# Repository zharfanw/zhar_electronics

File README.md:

# zhar_electronics
Database of Zharfan's Electronics 

## Tools 
  1. KiCAD
  2. Altium
  3. EasyEDA

## Electronics Theme
### Power Distribution Module MOSFET DC
  1. [Single Switch PDM](/SingleSwitchControlPDM/)
  2. 
### Power Distribution Module Relay
  1. Single Relay :soon:
  2. 4 Channel Relay :soon:
  3. 8 Channel Relay :soon:
  4. 8 Channel Relay via I2C :soon:
### ESP32 Universe
  1. [ESP32 Raw](/ESP32Raw/)
### At Tiny uC Universe
  1. [At Tiny Raw](/AtTinyRaw_1) 
  2. [At Tiny 3216 DevBoard](/ATTiny3216_DevBoard) 
### Power Button 
  1. [External Latch Power Button](/ExternalLatchPowerButton_Raw)
  2. [Smart Power Button Latch](/LTC2954_ModuleConnector/)
  3. [Latch Power Button with Trigger](/LatchPowerButtonWithTrig_Module/)
### DCDC Converter
  1. [Non Inverting Buck Boost Converter SEPIC MT3608](/Non%20Inverting%20Buck_Boost%20Converter%20Sepic%20MT3608/) 
  2. [78xx Replacement](/78xx%20Replacement/)
  3. [DCDC Boost Converter XL6009](/DCDC%20Boost%20Converter%20XL6009/)

### Power Bank Batttery Management System
 1. [Power Bank IP5306](/PowerBank_IP5306)

### Instrumentation Signal Conditioning
 1. 4-20mA to 0-5v Converter :soon:
 2. 4-20mA to 0-3v Converter :soon:
 5. Inverting Op Amp
 6. Non-Inverting Op Amp

### Display 
  1. OLED
  2. 7 Segment
  3. Dot Matrix
  4. HMI
  5. LCD

### Sensor IC
  1. MPU6050
  2. Accelerometer
  3. Barometric
  4. 

### Analog Multiplexer :soon:
:arrows_counterclockwise:
### Digital Multiplexer :soon:
:arrows_counterclockwise:
### Signal Generator :soon:
:arrows_counterclockwise:
### DC Motor Controller :soon:
:arrows_counterclockwise:
### Formula Student :soon:
:arrows_counterclockwise:

### Engine Ignition System :soon:
:arrows_counterclockwise:
### Mosfet Driver :soon:
:arrows_counterclockwise:

## Regerence Design

### Multimeter/Oscilloscope 
  1. [STM32 Scopev1](https://oshwlab.com/radiohonza/stm32ez-scopev1_copy)
  2. [STM32 Multimeter](https://hackaday.io/project/165857-stm32-open-source-multimeter)

### Nucleo Series STM32 (Need to Copy)()
 1. [Nucleo 64 STM32F446RE]
 2. [Nucleo 144 STM32]

### BLDC/PMSM/AC Motor Controller :soon:
  1. [Referensi VESC Controller](https://github.com/paltatech/VESC-controller)
  2. 

### Engine Control Unit
 1. [Referensi Speeduino](https://github.com/speeduino)
 2. [Referensi rusEFI](https://github.com/rusefi)

### FPGA Board by Olimex
 1. [Referensi Olimex](https://github.com/OLIMEX/iCE40HX8K-EVB)
 2. [Referensi Olimex 1](https://github.com/OLIMEX/iCE40HX1K-EVB)
 3. [Referensi Olimex FPGA Daughter ADC](https://www.olimex.com/Products/FPGA/iCE40/iCE40-ADC/open-source-hardware)
 4. [Referensi Olimex FPGA Daughter DAC](https://www.olimex.com/Products/FPGA/iCE40/iCE40-DAC/open-source-hardware)
 5. [Referensi Olimex FPGA Daughter VGA, PS/2 and IrDA link](https://www.olimex.com/Products/FPGA/iCE40/iCE40-IO/open-source-hardware)
 6. [Referensi Olimex FPGA Daughter DIO](https://www.olimex.com/Products/FPGA/iCE40/iCE40-DIO/open-source-hardware)

### Referensi from Wagiminator(Need To Copy) (2/66 Coppied)
 1. [IP5306 LiPo Charger Booster SMD (Copied)](https://oshwlab.com/wagiminator/y-ip5306-lipo-charger-booster)
 2. [ATmega SolderingStation SMD v2](https://oshwlab.com/wagiminator/z-solderingstation-smd-v2)
 3. [ATmega TransistorTester SMD](https://oshwlab.com/wagiminator/y-atmega-transistortester-smd)
 4. [ATtiny84 TinyHVSP SMD](https://oshwlab.com/wagiminator/z-attiny84-tinyhvprogrammer)
 5. [y-atmega-eeprom-programmer](https://oshwlab.com/wagiminator/y-atmega-eeprom-programmer)
 6. [y-attiny814-power-analyzer](https://oshwlab.com/wagiminator/y-attiny814-power-analyzer
)
 7. (https://oshwlab.com/wagiminator/adum3160-usb-isolator
)
8. (https://oshwlab.com/wagiminator/attiny13-tinytacho
)

9. (https://oshwlab.com/wagiminator/attiny13-tinyups-smd
)

10. (https://oshwlab.com/wagiminator/attiny85-phone-charge-guard
)
11. (https://oshwlab.com/wagiminator/samd21e-development-board
)

12. (https://oshwlab.com/wagiminator/attiny814-nrf2usb
)

13. (https://oshwlab.com/wagiminator/y-attiny10-development-board-smd
)

14. [IP5306 LiPo Charger Booster USB-C (Copied)](https://oshwlab.com/wagiminator/ip5306-lipo-charger-booster-usb-c
)

15. (https://oshwlab.com/wagiminator/lipo-charger-protector-booster_copy
)

17. (https://oshwlab.com/wagiminator/attiny13-tinyremoteir-xl
)

18. (https://oshwlab.com/wagiminator/y-mt3608-12v-boost-converter
)
19. (https://oshwlab.com/wagiminator/attiny1604-updi-hv-programmer
)
20. (https://oshwlab.com/wagiminator/tp4056-lipo-charger-ls
)
21. (https://oshwlab.com/wagiminator/y-lm2596-5vbuckconverter-smd
)
22. (https://oshwlab.com/wagiminator/y-tp4056-lir2032-charger
)
23. (https://oshwlab.com/wagiminator/y-mp2307-5vbuckconverter-smd
)
24. (https://oshwlab.com/wagiminator/y-attiny13-soldering-station-smd
)
25. (https://oshwlab.com/wagiminator/z-mc34063-5v-buckconverter
)
26. (https://oshwlab.com/wagiminator/cn3058-lifepo4-power-board-ls-3v3
)
27. (https://oshwlab.com/wagiminator/cn3058-lifepo4-power-board-ls-5v
)
28. (https://oshwlab.com/wagiminator/tp4056-lipo-charger-protector-power-booster_copy_copy
)
29. (https://oshwlab.com/wagiminator/attiny84-tinycalibrator
)
30. (https://oshwlab.com/wagiminator/attiny13-tinyradio
)
31. (https://oshwlab.com/wagiminator/attiny85-usb-c-tester
)
32. (https://oshwlab.com/wagiminator/tp4056-lipo-charger-protector-power-booster_copy
)
33. (https://oshwlab.com/wagiminator/y-cn3801-lifepo4-solar-charger_copy_copy
)
34. (https://oshwlab.com/wagiminator/attiny814-usb-rtc
)
35. (https://oshwlab.com/wagiminator/y-attiny85-electronic-load
)
36. (https://oshwlab.com/wagiminator/z-lifepo4-charger
)
37. (https://oshwlab.com/wagiminator/lipo-charger-protector-booster
)
38. (https://oshwlab.com/wagiminator/fp6277-power-bank
)
39. (https://oshwlab.com/wagiminator/pyupdi-programmer_copy_copy
)
40. (https://oshwlab.com/wagiminator/pyupdi-programmer
)
41. (https://oshwlab.com/wagiminator/atmega-updi-hv-programmer
)
42. (https://oshwlab.com/wagiminator/attiny13-tinyremote-rf
)

43. (https://oshwlab.com/wagiminator/attiny-814-development-board-smd
)

44. (https://oshwlab.com/wagiminator/y-tps61169-boost-led-driver
)

45. (https://oshwlab.com/wagiminator/attiny84-development-board-smd
)

46. (https://oshwlab.com/wagiminator/y-ch330-usb2serialconverter-3v3-smd
)

47. (https://oshwlab.com/wagiminator/samd11c-swd-programmer
)

48. (https://oshwlab.com/wagiminator/mp2307-usb-c-buck-converter
)

49. (https://oshwlab.com/wagiminator/attiny45-usbtinyisp-smd
)

50. (https://oshwlab.com/wagiminator/attiny1604-updi-programmer
)

51. (https://oshwlab.com/wagiminator/y-cn3058-lifepo4-charger-booster
)

52. (https://oshwlab.com/wagiminator/samd11d-development-board
)

53. (https://oshwlab.com/wagiminator/y-attiny45-usbtinyisp
)

54. (https://oshwlab.com/wagiminator/y-max3000-altera-cpld-development-board_copy
)

55. (https://oshwlab.com/wagiminator/samd11c-development-board
)

56. (https://oshwlab.com/wagiminator/swd-programmer-adapter
)

57. (https://oshwlab.com/wagiminator/attiny85-development-board-dip
)
58. (https://oshwlab.com/wagiminator/attiny85-development-board-smd
)
59. (https://oshwlab.com/wagiminator/attiny-814-development-board-smd_copy
)
60. (https://oshwlab.com/wagiminator/attiny412-5v-isolated-dc-dc-converter
)
61. (https://oshwlab.com/wagiminator/attiny412-5v-isolated-dual-supply
)
62. (https://oshwlab.com/wagiminator/1541-ii-power-guard
)
63. (https://oshwlab.com/wagiminator/ip2312-li-ion-charger
)
64. (https://oshwlab.com/wagiminator/usb-power-filter
)
65. (https://oshwlab.com/wagiminator/attiny412-usb-pd-inverter
)
66. (https://oshwlab.com/wagiminator/ip6520-usb-pd-source)

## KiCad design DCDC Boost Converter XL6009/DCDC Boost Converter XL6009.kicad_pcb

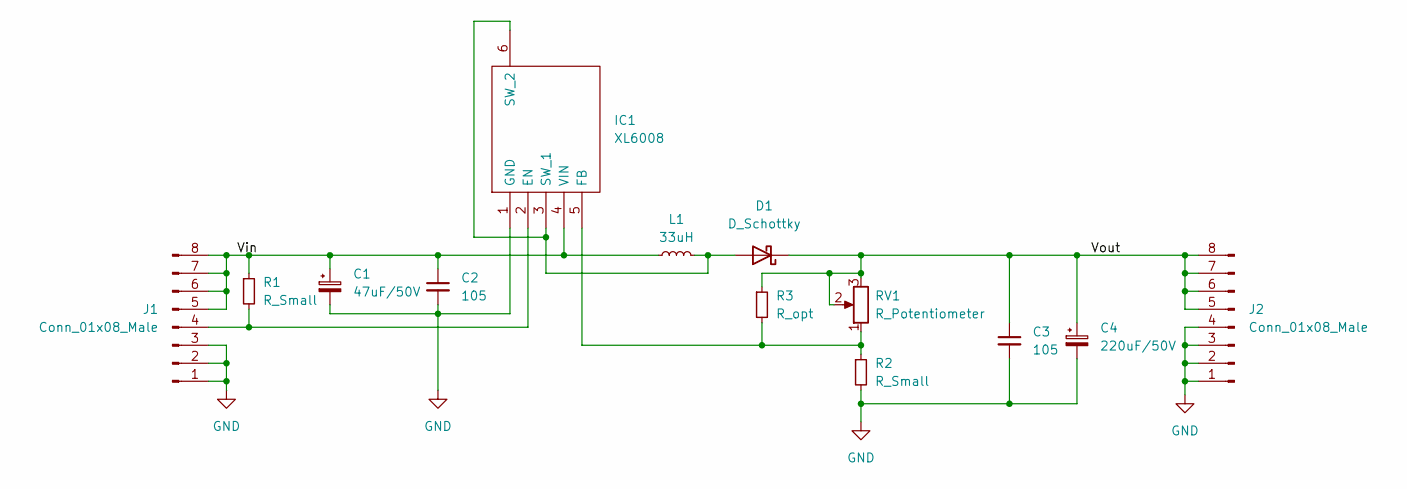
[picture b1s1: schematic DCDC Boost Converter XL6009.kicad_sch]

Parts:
C1: 47uF/50V; CP_Elec_6.3x5.9
C2, C3: 105; C_0805_2012Metric_Pad1.18x1.45mm_HandSolder
C4: 220uF/50V; CP_Elec_6.3x5.9
D1: D_Schottky; D_SMA-SMB_Universal_Handsoldering
IC1: XL6008; Manufacturer_Part_Number XL6008
J1, J2: Conn_01x08_Male; PinSocket_1x08_P2.54mm_Vertical
L1: 33uH; L_10.4x10.4_H4.8
R1, R2: R_Small; R_0805_2012Metric_Pad1.20x1.40mm_HandSolder
R3: R_opt; R_0805_2012Metric_Pad1.20x1.40mm_HandSolder
RV1: R_Potentiometer; Potentiometer_Bourns_3296W_Vertical

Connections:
/Vin: C1.1, C2.1, IC1.4 (VIN), J1.5, J1.6, J1.7, J1.8, L1.1, R1.1
/Vout: C3.1, C4.1, D1.1 (K), J2.5, J2.6, J2.7, J2.8, R3.1, RV1.2, RV1.3
GND: C1.2, C2.2, C3.2, C4.2, IC1.1 (GND), J1.1, J1.2, J1.3, J2.1, J2.2, J2.3, J2.4, R2.2
unnamed: D1.2 (A), IC1.3 (SW_1), IC1.6 (SW_2), L1.2
unnamed: IC1.2 (EN), J1.4, R1.2
unnamed: IC1.5 (FB), R2.1, R3.2, RV1.1

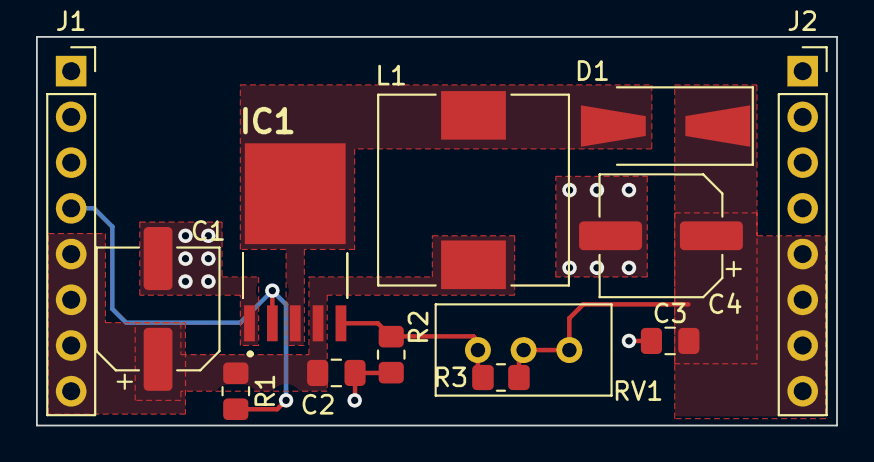
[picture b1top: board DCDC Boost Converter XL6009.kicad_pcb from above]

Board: 2 copper layers, 44.5 x 21.6 mm, 13 parts (0 on the bottom side), 6 nets.

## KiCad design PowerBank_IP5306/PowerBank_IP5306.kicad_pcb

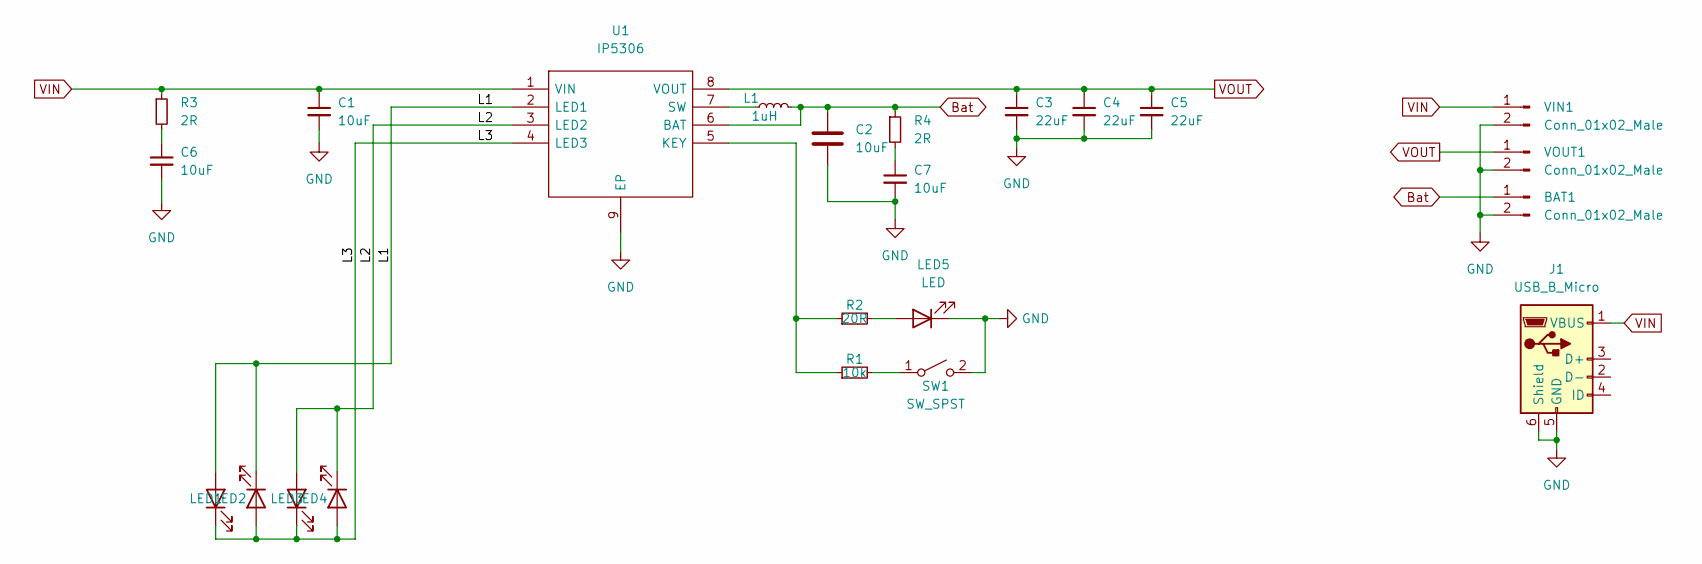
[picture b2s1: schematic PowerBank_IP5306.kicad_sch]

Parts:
BAT1: Conn_01x02_Male; PinHeader_1x02_P2.54mm_Vertical
C1, C2, C6, C7: 10uF; C_0805_2012Metric
C3, C4, C5: 22uF; C_0805_2012Metric
J1: USB_B_Micro; USB_Micro-B_Molex-105017-0001
L1: 1uH
LED1, LED2, LED3, LED4, LED5: LED; D_0805_2012Metric
R1: 10k; R_0805_2012Metric
R2: 20R; R_0805_2012Metric
R3, R4: 2R; R_0805_2012Metric
SW1: SW_SPST; SW_SPST_B3U-1000P
U1: IP5306; SOIC127P600X165-9N; Manufacturer_Part_Number IP5306
VIN1: Conn_01x02_Male; PinHeader_1x02_P2.54mm_Vertical
VOUT1: Conn_01x02_Male; PinHeader_1x02_P2.54mm_Vertical

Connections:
/L1: LED1.2 (A), LED2.1 (K), U1.2 (LED1)
/L2: LED3.2 (A), LED4.1 (K), U1.3 (LED2)
/L3: LED1.1 (K), LED2.2 (A), LED3.1 (K), LED4.2 (A), U1.4 (LED3)
Bat: BAT1.1, C2.1, L1.2, R4.1, U1.6 (BAT)
GND: BAT1.2, C1.2, C2.2, C3.2, C4.2, C5.2, C6.2, C7.2, J1.5 (GND), J1.6 (Shield), LED5.1 (K), SW1.2 (B), U1.9 (EP), VIN1.2, VOUT1.2
unnamed: L1.1, U1.7 (SW)
unnamed: LED5.2 (A), R2.2
unnamed: R1.2, SW1.1 (A)
unnamed: R1.1, R2.1, U1.5 (KEY)
unnamed: C6.1, R3.2
unnamed: C7.1, R4.2
VIN: C1.1, J1.1 (VBUS), R3.1, U1.1 (VIN), VIN1.1
VOUT: C3.1, C4.1, C5.1, U1.8 (VOUT), VOUT1.1

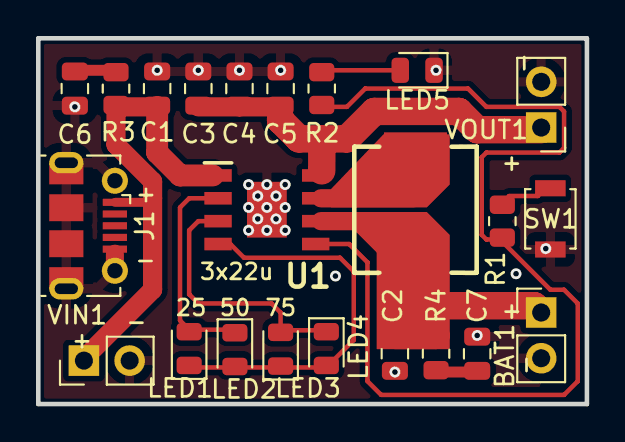
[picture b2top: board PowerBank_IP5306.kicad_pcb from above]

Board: 2 copper layers, 30.5 x 20.3 mm, 23 parts (0 on the bottom side), 13 nets.

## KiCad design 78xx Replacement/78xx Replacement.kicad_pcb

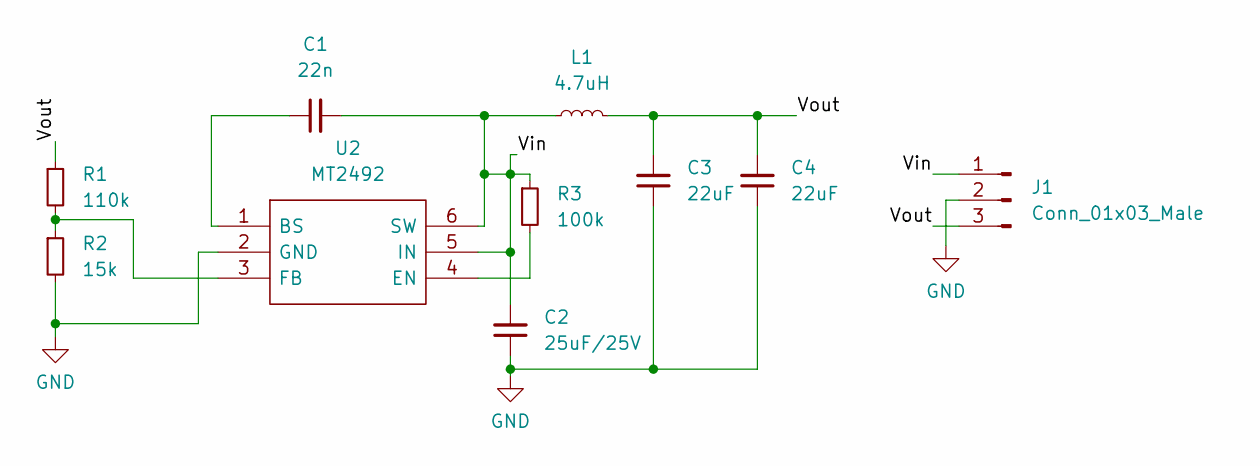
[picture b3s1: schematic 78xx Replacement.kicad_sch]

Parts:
C1: 22n; C_0603_1608Metric
C2: 25uF/25V; C_0603_1608Metric
C3, C4: 22uF; C_0603_1608Metric
J1: Conn_01x03_Male; PinHeader_1x03_P2.54mm_Horizontal
L1: 4.7uH; L_7.3x7.3_H4.5
R1: 110k; R_0805_2012Metric
R2: 15k; R_0805_2012Metric
R3: 100k; R_0805_2012Metric
U2: MT2492; SOT95P280X145-6N; Manufacturer_Part_Number MT2492

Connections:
/Vin: C1.2, C2.2, J1.1, L1.1, R3.1, U2.5 (IN), U2.6 (SW)
/Vout: C3.2, C4.2, J1.3, L1.2, R1.1
GND: C2.1, C3.1, C4.1, J1.2, R2.2, U2.2 (GND)
unnamed: C1.1, U2.1 (BS)
unnamed: R1.2, R2.1, U2.3 (FB)
unnamed: R3.2, U2.4 (EN)

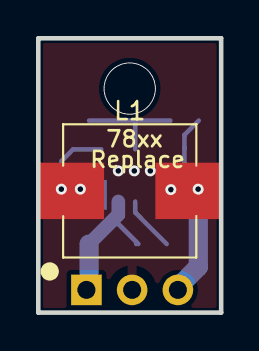
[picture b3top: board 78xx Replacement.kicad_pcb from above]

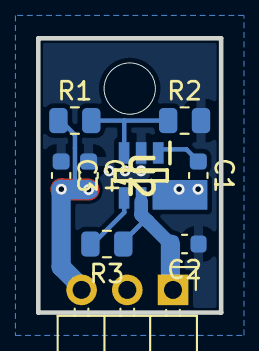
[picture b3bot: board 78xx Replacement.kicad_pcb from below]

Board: 2 copper layers, 10.2 x 15.2 mm, 10 parts (9 on the bottom side), 6 nets.

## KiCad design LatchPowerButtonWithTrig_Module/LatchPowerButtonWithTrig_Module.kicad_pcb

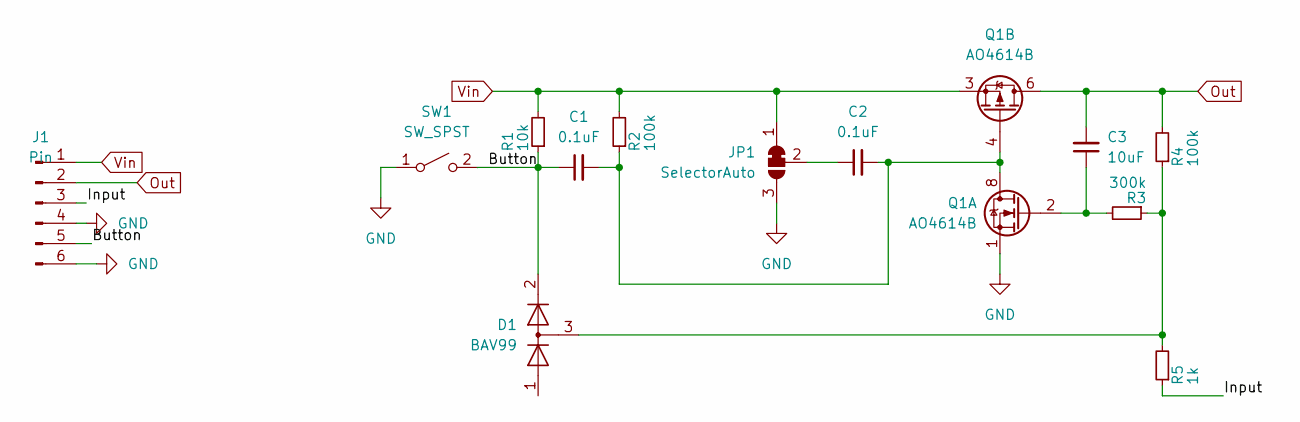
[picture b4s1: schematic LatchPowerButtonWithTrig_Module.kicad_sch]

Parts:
C1, C2: 0.1uF; C_0805_2012Metric_Pad1.18x1.45mm_HandSolder
C3: 10uF; C_1206_3216Metric_Pad1.33x1.80mm_HandSolder
D1: BAV99; SOT-23
J1: Pin; PinHeader_1x06_P2.54mm_Vertical
JP1: SelectorAuto; SolderJumper-3_P1.3mm_Bridged12_Pad1.0x1.5mm
Q1: AO4614B; SOIC-8_3.9x4.9mm_P1.27mm
R1: 10k; R_0805_2012Metric_Pad1.20x1.40mm_HandSolder
R2, R4: 100k; R_0805_2012Metric_Pad1.20x1.40mm_HandSolder
R3: 300k; R_0805_2012Metric_Pad1.20x1.40mm_HandSolder
R5: 1k; R_0805_2012Metric_Pad1.20x1.40mm_HandSolder
SW1: SW_SPST; SW_SPST_CK_RS282G05A3

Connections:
/Button: C1.1, D1.2 (A), J1.5, R1.1, SW1.2 (B)
/Input: J1.3, R5.1
GND: J1.4, J1.6, JP1.3 (B), Q1.1 (S), SW1.1 (A)
unnamed: C1.2, C2.2, Q1.4 (G), Q1.7 (D), Q1.8 (D), R2.1
unnamed: C2.1, JP1.2 (C)
unnamed: C3.1, Q1.2 (G), R3.2
unnamed: D1.3 (K), R3.1, R4.1, R5.2
Out: C3.2, J1.2, Q1.5 (D), Q1.6 (D), R4.2
Vin: J1.1, JP1.1 (A), Q1.3 (1), R1.2, R2.2

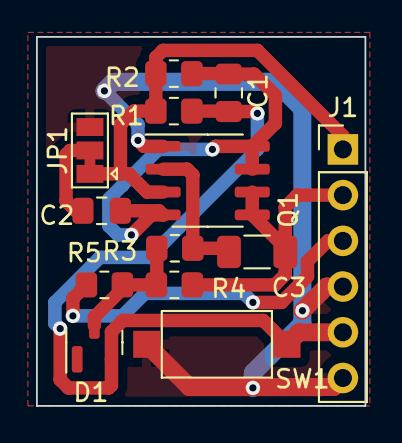
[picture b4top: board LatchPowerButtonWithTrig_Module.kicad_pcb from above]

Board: 2 copper layers, 18.2 x 20.5 mm, 13 parts (0 on the bottom side), 9 nets.

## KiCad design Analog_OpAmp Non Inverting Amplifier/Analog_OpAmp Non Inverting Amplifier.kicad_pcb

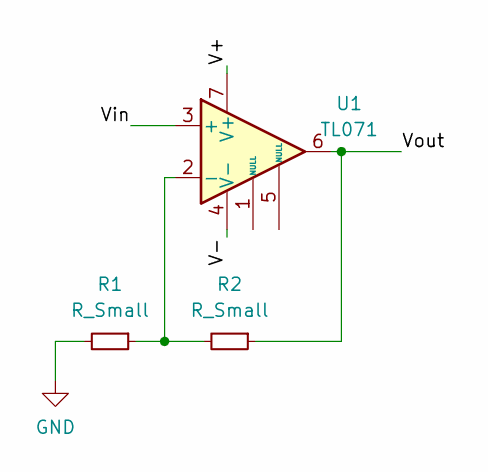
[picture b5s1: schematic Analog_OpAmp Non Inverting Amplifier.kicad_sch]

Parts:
R1, R2: R_Small; R_0805_2012Metric_Pad1.20x1.40mm_HandSolder
U1: TL071; DIP-8_W7.62mm_LongPads

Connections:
/V+: U1.7 (V+)
/V-: U1.4 (V-)
/Vin: U1.3 (+)
/Vout: R2.1, U1.6
GND: R1.2
unnamed: R1.1, R2.2, U1.2 (-)

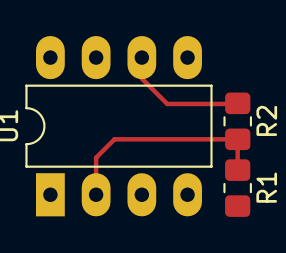
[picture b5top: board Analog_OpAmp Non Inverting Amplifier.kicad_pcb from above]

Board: 2 copper layers, 3 parts (0 on the bottom side), 2 nets.

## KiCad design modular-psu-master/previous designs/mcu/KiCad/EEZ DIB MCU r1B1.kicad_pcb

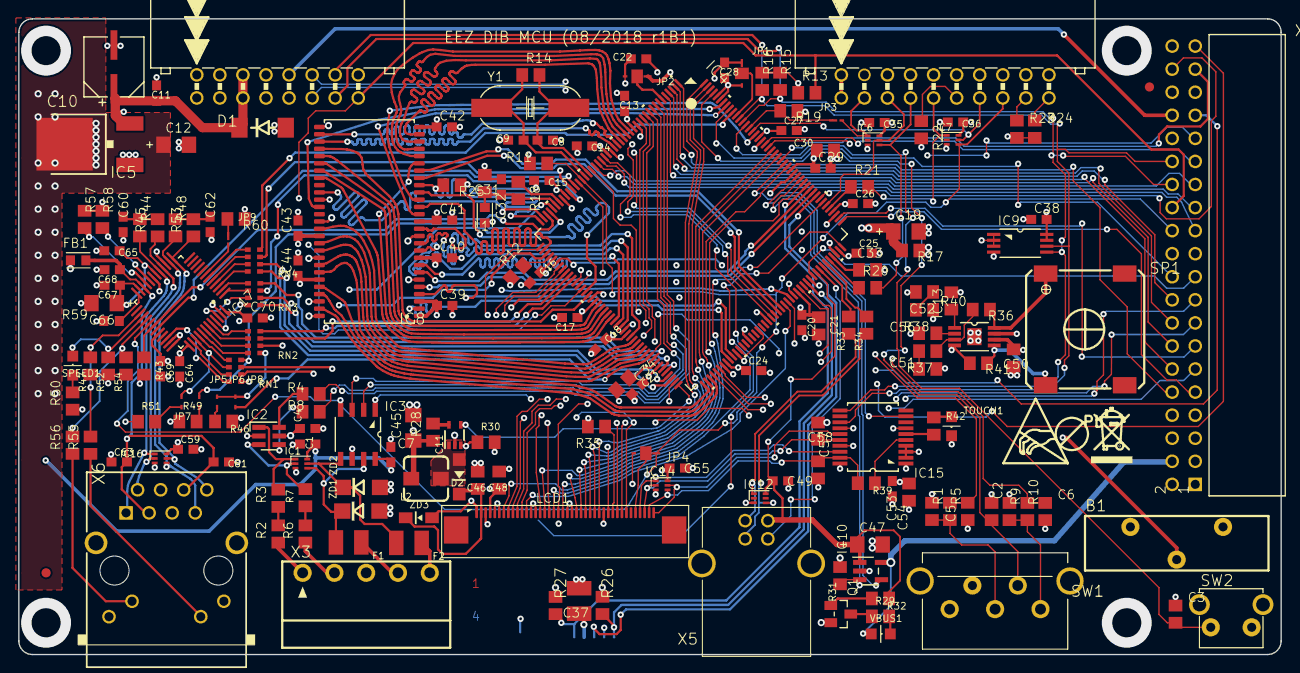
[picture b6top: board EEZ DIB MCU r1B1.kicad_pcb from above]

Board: 4 copper layers, 139.0 x 70.0 mm, 193 parts (0 on the bottom side), 233 nets.

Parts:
B1: DS1092-16-B6P
C1, C4, C7, C11, C13, C14, C15, C16, C17, C18, C20, C23, C24, C25, C26, C27, C28, C29, C32, C35, C36, C38, C39, C40, C41, C42, C43, C44, C49, C53, C55, C59, C60, C61, C62, C63, C64, C65, C67, C68, C69, C70: 100n; C0603
C2, C3, C5, C6, C57, C58: 10n; C0805
C8, C9: 18p; C0603
C10: 47u; CAPAE660X610N
C12, C66: 10u; EC1206
C19: 4u7; EC1206
C21, C30, C31, C46, C50, C54: 1u; C0805
C22: N.C.; C0603
C33, C34, C48: 2u2; C0805
C37: 10u; C1210
C45: 4u7; C1206
C47: 4u7/16V (293D475X9016A2TE3); EC1206
C51, C52: 470n; C0805
C56: 220n; C0805
D1: SMBJ5.0A-TR; DO214AA
D2: NSR0240; SOD123
EEZ_SIGNATURE: SIGNATURESMALL; SIGNATURE_5MM
F1, F2: 50mA; F1210
FB1: 60R@100MHz; BEAD0603
FM1, FM2: FIDUCIAL
IC1, IC6, IC7, IC12, IC14, IC16: TPD4E001DRLR; DRL6
IC2: SN74LVC2G34DBVR; DBV6
IC3: BTS3408G; SOIC127P600X173-8N
IC4: STM32F769IGT6; LQFP-176_24X24MM
IC5: LD1117ADT33TR; DPACK
IC8: IS42S16400J; TSOPII-54
IC9: BR24G64FVT-3AGE2; PW8_TSSOP8
IC10: TPS2051BDBVR; DBV5
IC11: TPS61169DCKR; DCK5
IC13: TPA6205A1DGN; SOP65P490X110-9N
IC15: AR1021-I/SS; SOP65P780X200-20N
IC17: DP83848CVV_NOPB; PT48
J1: 5033981892
JP1, JP2, JP4: JP3-CUT
JP3, JP9: JP2-NOCUT
JP5, JP6, JP7, JP8: JP2-CUT
L1: LCBA-600; BEAD0603
L2: DLG-0403-4R7; DE0403
LCD1: PCA-6-LA-40-HL-3; FPC_40
Q1: MMBT5551; SOT23-BEC
R1, R2, R3, R6, R7, R9, R13, R15, R16, R42: 4K7; R0805
R4, R8: 1K; R0805
R5, R10, R11, R12, R22, R23, R24, R25, R35, R37, R38: 10K; R0805
R14: 1M; R0805
R17: 0R; R0805
R18: 47R; R0805
R19, R26, R27, R29, R31, R32, R40: 47K; R0805
R20, R21, R33, R34: 22R; R0805
R28, R30: 10R; R0805
R36, R39, R41: 20K; R0805
R43: 1K5; R0805
R44, R45, R48, R53: 49R9; R0805
R46, R47, R49, R51, R52, R54, R57, R58, R60: 2K2; R0805
R50, R55, R56: 220R; R0805
R59: 4K87; R0603
RN1, RN2, RN3, RN4: DR1206-33R-4/8; CAY16
SP1: LD-BZEL-M1313
SPEED1: HSMY-C170; LED_0805
SW1: PEC16-2215F-S0024; PEC16-2215F
SW2: BSF-3152; BSF-315X
TOUCH1: HSMY-C170; LED_0805
U$1: RECYCLE_BIN1_8
U$5: PB_SMALL
U$6: ESD_SYMBOL
VBUS1: HSMG-C170; LED_0805
X1: ZL263-40DG
X2: ZL231-16KG; ML16L
X3: 1844249; MC1,5_5-G-3,5
X4: ZL231-20KG; ML20L
X5: 292304-1; USB-B
X6: LMJTAB881243M-L; RJ45-TRAFO-LED
Y1: 10MHz; HC-49_4H
ZD1, ZD2: SMAJ18A; DO214AC
ZD3: BZX384-B30.115; SOD323-W

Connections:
+3V3: C4.1, C12.+, C35.1, C36.1, C37.1, C38.2, C39.1, C40.1, C41.1, C42.1, C43.1, C44.1, C45.1, C48.1, C50.2, C53.2, C54.2, C55.2, C59.1, C69.1, C70.1, FB1.P$1, IC2.5, IC5.4, IC6.6, IC7.6, IC8.1, IC8.3, IC8.9, IC8.14, IC8.27, IC8.43, IC8.49, IC9.1, IC9.2, IC9.3, IC9.7, IC9.8, IC13.6, IC14.6, IC15.1, IC16.6, IC17.32, IC17.48, J1.4, L2.1, LCD1.4, R1.1, R9.1, R13.1, R15.1, R16.1, R17.1, R19.1, R25.1, R26.1, R27.1, R28.1, R31.2, R35.2, R40.2, R43.2, R47.1, R50.1, R51.1, R52.1, R54.1, R57.1, R58.1, R60.1, X1.32, X2.16, X4.1, X4.2, X6.9, X6.12
+3V3(A): C61.2, C63.2, C68.1, FB1.P$2, IC17.22, X6.3, X6.6
+5V: C1.1, C7.2, C10.1, C11.1, D1.C, IC1.6, IC3.8, IC5.3, IC10.5, VBUS1.A, X1.3, X1.4, X2.5, X2.6
+12V: X1.5, X1.6, X2.3, X2.4
/Ethernet PHY/ETH_COL: IC4.47, RN2.2
/Ethernet PHY/ETH_CRS: IC4.40, JP5.1, RN1.4
/Ethernet PHY/ETH_MDC: IC4.33, IC17.31
/Ethernet PHY/ETH_MDIO: IC4.42, IC17.30, R43.1
/Ethernet PHY/ETH_RXD0: IC4.54, RN2.3
/Ethernet PHY/ETH_RXD1: IC4.55, RN2.4
/Ethernet PHY/ETH_RXD2: IC4.83, RN3.1
/Ethernet PHY/ETH_RXD3: IC4.84, RN3.2
/Ethernet PHY/ETH_RX_CLK: IC4.41, RN1.2
/Ethernet PHY/ETH_RX_DV: IC4.53, RN1.3
/Ethernet PHY/ETH_TXD0: IC4.85, RN4.1
/Ethernet PHY/ETH_TXD1: IC4.86, RN4.2
/Ethernet PHY/ETH_TXD2: IC4.34, RN4.3
/Ethernet PHY/ETH_TXD3: IC4.167, RN4.4
/Ethernet PHY/ETH_TX_CLK: IC4.35, RN3.3
/Ethernet PHY/ETH_TX_EN: IC4.80, RN3.4
/Ethernet PHY/LED_ACT: IC17.26, R47.2, R55.2
/Ethernet PHY/LED_LINK: IC17.28, R54.2, R56.2
/Ethernet PHY/LED_SPEED: IC17.27, R52.2, SPEED1.C
/Ethernet PHY/MCLK_25: IC4.122, RN1.1
/I/O connectors, encoders, user SW/+VAUX: X1.34, X2.10
/I/O connectors, encoders, user SW/ENC_A: C5.2, IC4.119, R5.1
/I/O connectors, encoders, user SW/ENC_B: C6.1, IC4.120, R10.1
/I/O connectors, encoders, user SW/ENC_SW: C2.2, IC4.173, SW1.E
/I/O connectors, encoders, user SW/USER_SW: C3.2, IC4.163, SW2.1
/SDRAM, JTAG, SD card, EEPROM/DBGACK: R24.1, X4.19
/SDRAM, JTAG, SD card, EEPROM/DBGRQ: R23.1, X4.17
/SDRAM, JTAG, SD card, EEPROM/FMC_A0: IC4.16, IC8.23
/SDRAM, JTAG, SD card, EEPROM/FMC_A1: IC4.17, IC8.24
/SDRAM, JTAG, SD card, EEPROM/FMC_A2: IC4.18, IC8.25
/SDRAM, JTAG, SD card, EEPROM/FMC_A3: IC4.19, IC8.26
/SDRAM, JTAG, SD card, EEPROM/FMC_A4: IC4.20, IC8.29
/SDRAM, JTAG, SD card, EEPROM/FMC_A5: IC4.21, IC8.30
/SDRAM, JTAG, SD card, EEPROM/FMC_A6: IC4.60, IC8.31
/SDRAM, JTAG, SD card, EEPROM/FMC_A7: IC4.63, IC8.32
/SDRAM, JTAG, SD card, EEPROM/FMC_A8: IC4.64, IC8.33
/SDRAM, JTAG, SD card, EEPROM/FMC_A9: IC4.65, IC8.34
/SDRAM, JTAG, SD card, EEPROM/FMC_A10: IC4.66, IC8.22
/SDRAM, JTAG, SD card, EEPROM/FMC_A11: IC4.67, IC8.35
/SDRAM, JTAG, SD card, EEPROM/FMC_BA0: IC4.112, IC8.20
/SDRAM, JTAG, SD card, EEPROM/FMC_BA1: IC4.113, IC8.21
/SDRAM, JTAG, SD card, EEPROM/FMC_D0: IC4.97, IC8.2
/SDRAM, JTAG, SD card, EEPROM/FMC_D1: IC4.98, IC8.4
/SDRAM, JTAG, SD card, EEPROM/FMC_D2: IC4.142, IC8.5
/SDRAM, JTAG, SD card, EEPROM/FMC_D3: IC4.143, IC8.7
/SDRAM, JTAG, SD card, EEPROM/FMC_D4: IC4.68, IC8.8
/SDRAM, JTAG, SD card, EEPROM/FMC_D5: IC4.69, IC8.10
/SDRAM, JTAG, SD card, EEPROM/FMC_D6: IC4.70, IC8.11
/SDRAM, JTAG, SD card, EEPROM/FMC_D7: IC4.73, IC8.13
/SDRAM, JTAG, SD card, EEPROM/FMC_D8: IC4.74, IC8.42
/SDRAM, JTAG, SD card, EEPROM/FMC_D9: IC4.75, IC8.44
/SDRAM, JTAG, SD card, EEPROM/FMC_D10: IC4.76, IC8.45
/SDRAM, JTAG, SD card, EEPROM/FMC_D11: IC4.77, IC8.47
/SDRAM, JTAG, SD card, EEPROM/FMC_D12: IC4.78, IC8.48
/SDRAM, JTAG, SD card, EEPROM/FMC_D13: IC4.89, IC8.50
/SDRAM, JTAG, SD card, EEPROM/FMC_D14: IC4.90, IC8.51
/SDRAM, JTAG, SD card, EEPROM/FMC_D15: IC4.91, IC8.53
/SDRAM, JTAG, SD card, EEPROM/FMC_NBL0: IC4.169, IC8.15
/SDRAM, JTAG, SD card, EEPROM/FMC_NBL1: IC4.170, IC8.39
/SDRAM, JTAG, SD card, EEPROM/FMC_SDCKE0: IC4.43, IC8.37
/SDRAM, JTAG, SD card, EEPROM/FMC_SDCLK: IC4.116, IC8.38
/SDRAM, JTAG, SD card, EEPROM/FMC_SDNCAS: IC4.160, IC8.17
/SDRAM, JTAG, SD card, EEPROM/FMC_SDNE0: IC4.44, IC8.19, R25.2
/SDRAM, JTAG, SD card, EEPROM/FMC_SDNRAS: IC4.59, IC8.18
/SDRAM, JTAG, SD card, EEPROM/FMC_SDNWE: IC4.46, IC8.16
/SDRAM, JTAG, SD card, EEPROM/RTCK: R22.1, X4.11
/SDRAM, JTAG, SD card, EEPROM/SDMMC1_CK: IC4.141, J1.5
/SDRAM, JTAG, SD card, EEPROM/SDMMC1_CMD: IC4.144, J1.3, R27.2
/SDRAM, JTAG, SD card, EEPROM/SDMMC1_D0: IC4.121, J1.7, R26.2
/SDRAM, JTAG, SD card, EEPROM/SD_DETECT: IC4.24, J1.SW1
/SDRAM, JTAG, SD card, EEPROM/SYS_JTCK-SWCLK: IC4.137, R21.1
/SDRAM, JTAG, SD card, EEPROM/SYS_JTDI: IC4.138, IC6.5, X4.5
/SDRAM, JTAG, SD card, EEPROM/SYS_JTDO-SWO: IC4.161, IC7.5, X4.13
/SDRAM, JTAG, SD card, EEPROM/SYS_JTMS-SWDIO: IC4.128, R20.1
/SDRAM, JTAG, SD card, EEPROM/SYS_JTRST: IC4.162, JP3.1, R19.2
/SDRAM, JTAG, SD card, EEPROM/TCK: IC7.1, R21.2, X4.9
/SDRAM, JTAG, SD card, EEPROM/TMS: IC6.4, R20.2, X4.7
/STM32F7 MCU/BOOT0: IC4.166, JP1.COM
/STM32F7 MCU/BYPASS_REG: IC4.48, R12.2
/STM32F7 MCU/DAC_OUT1: C52.2, IC4.50
/STM32F7 MCU/IRQ_TOUCH: IC4.151, IC15.9
/STM32F7 MCU/LTDC_B2: IC4.150, LCD1.23
/STM32F7 MCU/LTDC_B3: IC4.154, LCD1.24
/STM32F7 MCU/LTDC_B4: IC4.155, LCD1.25
/STM32F7 MCU/LTDC_B5: IC4.174, LCD1.26
/STM32F7 MCU/LTDC_B6: IC4.175, LCD1.27
/STM32F7 MCU/LTDC_B7: IC4.176, LCD1.28
/STM32F7 MCU/LTDC_CLK: IC4.115, LCD1.30
/STM32F7 MCU/LTDC_DE: IC4.28, LCD1.34
/STM32F7 MCU/LTDC_G2: IC4.52, LCD1.15
/STM32F7 MCU/LTDC_G3: IC4.153, LCD1.16
/STM32F7 MCU/LTDC_G4: IC4.45, LCD1.17
/STM32F7 MCU/LTDC_G5: IC4.132, LCD1.18
/STM32F7 MCU/LTDC_G6: IC4.13, LCD1.19
/STM32F7 MCU/LTDC_G7: IC4.145, LCD1.20
/STM32F7 MCU/LTDC_HSYNC: IC4.12, LCD1.32
/STM32F7 MCU/LTDC_R2: IC4.139, LCD1.7
/STM32F7 MCU/LTDC_R3: IC4.56, LCD1.8
/STM32F7 MCU/LTDC_R4: IC4.51, LCD1.9
/STM32F7 MCU/LTDC_R5: IC4.32, LCD1.10
/STM32F7 MCU/LTDC_R6: IC4.57, LCD1.11
/STM32F7 MCU/LTDC_R7: IC4.114, LCD1.12
/STM32F7 MCU/LTDC_VSYNC: IC4.11, LCD1.33
/STM32F7 MCU/RCC_OSC_IN: C8.2, IC4.29, R14.2, Y1.2
/STM32F7 MCU/RCC_OSC_OUT: C9.2, IC4.30, R14.1, Y1.1
/STM32F7 MCU/TFT_BRIGHTNESS: IC4.88, IC11.4
/STM32F7 MCU/USB_OTG_FS_D_N: IC4.126, R33.2
/STM32F7 MCU/USB_OTG_FS_D_P: IC4.127, R34.2
/STM32F7 MCU/USB_OTG_FS_ID: IC4.125, X5.4
/STM32F7 MCU/USB_OTG_FS_PSO: IC4.147, IC10.4
/STM32F7 MCU/USB_OTG_FS_VBUS: C47.+, C49.2, IC4.124, IC10.1, IC12.6, R32.1, X5.1
/STM32F7 MCU/VBAT: IC4.6, JP2.COM
/STM32F7 MCU/VCAP1: C34.1, IC4.81
/STM32F7 MCU/VCAP2: C33.1, IC4.129
/STM32F7 MCU/VDDA: C31.1, C32.1, IC4.39, L1.P$2, R18.2
/STM32F7 MCU/VREF+: IC4.38, R18.1
/STM32F7 MCU/~USB_OTG_FS_OC: IC4.146, IC10.3, R31.1
/TFT, Audio, USB/LCD_DISP: LCD1.31, R35.1
/TFT, Audio, USB/USB_D_N: IC12.1, R33.1, X5.2
/TFT, Audio, USB/USB_D_P: IC12.4, R34.1, X5.3
/TFT, Audio, USB/VLED+: C46.1, D2.C, LCD1.2, ZD3.C
/TFT, Audio, USB/VLED-: IC11.3, LCD1.1, R30.1, ZD3.A
/TFT, Audio, USB/~AUDIO_SHDN: IC13.1, R40.1
DIN1: IC4.7, R4.2
DIN2: IC4.8, R8.2
DOUT1: IC3.2, IC4.9
DOUT2: IC3.3, IC4.10
GND: B1.1, B1.3, C1.2, C2.1, C3.1, C4.2, C5.1, C6.2, C7.1, C8.1, C9.1, C10.2, C11.2, C12.-, C13.2, C14.2, C15.2, C16.2, C17.2, C18.2, C19.-, C20.2, C21.2, C22.2, C23.2, C24.2, C25.2, C26.2, C27.2, C28.2, C29.2, C30.2, C31.2, C32.2, C33.2, C34.2, C35.2, C36.2, C37.2, C38.1, C39.2, C40.2, C41.2, C42.2, C43.2, C44.2, C45.2, C46.2, C47.-, C48.2, C49.1, C50.1, C51.2, C53.1, C54.1, C55.1, C56.1, C57.2, C58.2, C59.2, C60.2, C61.1, C62.2, C63.1, C64.2, C65.2, C66.-, C67.2, C68.2, C69.2, C70.2, D1.A, IC1.3, IC2.2, IC3.6, IC4.14, IC4.22, IC4.37, IC4.61, IC4.71, IC4.95, IC4.103, IC4.109, IC4.117, IC4.130, IC4.135, IC4.148, IC4.158, IC5.1, IC6.3, IC7.3, IC8.6, IC8.12, IC8.28, IC8.41, IC8.46, IC8.52, IC8.54, IC9.4, IC10.2, IC11.2, IC12.3, IC13.7, IC13.TP, IC14.3, IC15.2, IC15.3, IC15.4, IC15.7, IC15.14, IC15.17, IC15.20, IC16.3, IC17.15, IC17.19, IC17.35, IC17.36, IC17.47, J1.6, J1.S, J1.SW2, JP1.NC, JP4.NO, LCD1.3, LCD1.5, LCD1.6, LCD1.13, LCD1.14, LCD1.21, LCD1.22, LCD1.29, Q1.E, R12.1, R22.2, R23.2, R24.2, R30.2, R46.1, R49.1, R59.1, SW1.C, SW1.D, SW1.GND1, SW1.GND2, SW2.2, SW2.3, SW2.4, TOUCH1.C, X1.1, X1.2, X1.7, X1.8, X1.21, X1.22, X1.35, X1.36, X1.40, X2.7, X2.8, X2.9, X3.3, X4.4, X4.6, X4.8, X4.10, X4.12, X4.14, X4.16, X4.18, X4.20, X6.4, X6.5, ZD1.A, ZD2.A
I2C1_SCL: IC4.164, IC9.5, IC15.11, R15.2, X1.28, X2.13
I2C1_SDA: IC4.165, IC9.6, IC15.13, R16.2, X1.30, X2.14
unnamed: B1.2, JP2.NC
unnamed: C51.1, R37.2
unnamed: C52.1, R38.2
unnamed: C56.2, IC13.2
unnamed: C57.1, IC14.4, IC15.19, LCD1.39, R39.2
unnamed: C58.1, IC14.2, IC15.16, LCD1.38
unnamed: C60.1, R44.1, R45.2
unnamed: C62.1, R48.1, R53.2
unnamed: C64.1, C65.1, C66.+, C67.1, IC17.18, IC17.23, IC17.37
unnamed: D2.A, IC11.1, L2.2
unnamed: F1.1, X3.4
unnamed: F1.2, IC1.4, IC3.7, ZD1.C
unnamed: F2.1, X3.5
unnamed: F2.2, IC1.5, IC3.5, ZD2.C
unnamed: IC1.1, IC2.1, R3.2
unnamed: IC1.2, IC2.3, R7.2
unnamed: IC2.4, R8.1
unnamed: IC2.6, R4.1
unnamed: IC4.100, IC4.106
unnamed: IC6.1, JP3.2, X4.3
unnamed: IC11.5, R28.2
unnamed: IC13.3, R36.2, R37.1
unnamed: IC13.4, R38.1, R41.2
unnamed: IC13.5, R41.1, SP1.-
unnamed: IC13.8, R36.1, SP1.+
unnamed: IC14.1, IC15.18, LCD1.37
unnamed: IC14.5, IC15.15, LCD1.40
unnamed: IC15.5, R39.1
unnamed: IC15.6, R42.2
unnamed: IC16.1, IC17.17, R44.2, X6.1
unnamed: IC16.2, IC17.16, R45.1, X6.2
unnamed: IC16.4, IC17.14, R48.2, X6.7
unnamed: IC16.5, IC17.13, R53.1, X6.8
unnamed: IC17.1, RN3.6
unnamed: IC17.2, RN3.5
unnamed: IC17.3, RN4.8
unnamed: IC17.4, RN4.7
unnamed: IC17.5, RN4.6
unnamed: IC17.6, RN4.5
unnamed: IC17.7, JP9.2
unnamed: IC17.20, R58.2
unnamed: IC17.21, R57.2
unnamed: IC17.24, R59.2
unnamed: IC17.34, RN1.8
unnamed: IC17.38, RN1.7
unnamed: IC17.39, JP7.2, RN1.6
unnamed: IC17.40, RN1.5
unnamed: IC17.41, RN2.8
unnamed: IC17.42, RN2.7
unnamed: IC17.43, RN2.6
unnamed: IC17.44, RN2.5
unnamed: IC17.45, RN3.8
unnamed: IC17.46, RN3.7
unnamed: JP4.COM, LCD1.36
unnamed: JP5.2, R49.2
unnamed: JP6.1, JP8.1, RN2.1
unnamed: JP6.2, R46.2
unnamed: JP7.1, R51.2
unnamed: JP9.1, R60.2
unnamed: Q1.B, R32.2
unnamed: Q1.C, R29.1
unnamed: R1.2, R5.2, SW1.B
unnamed: R2.1, X3.1
unnamed: R2.2, R3.1
unnamed: R6.1, X3.2
unnamed: R6.2, R7.1
unnamed: R9.2, R10.2, SW1.A
unnamed: R29.2, VBUS1.C
unnamed: R42.1, TOUCH1.A
unnamed: R50.2, SPEED1.A
unnamed: R55.1, X6.11
unnamed: R56.1, X6.10
OE_SYNC: IC4.94, X1.39
OUT_PAR: IC4.140, X1.38
OUT_SER: IC4.152, X1.37
PE: X2.1, X2.2, X5.M1, X5.M2, X6.SH, X6.SH2
PWR_DIRECT: IC4.110, X2.12
PWR_SSTART: IC4.111, X2.11
SPI2_CLK: IC4.133, X1.9
SPI2_CSA: IC4.93, X1.15
SPI2_CSB: IC4.92, X1.17
SPI2_IRQ: IC4.123, X1.19
SPI2_MISO: IC4.87, X1.11
SPI2_MOSI: IC4.134, X1.13
SPI4_CLK: IC4.1, X1.10
SPI4_CSA: IC4.2, X1.16
SPI4_CSB: IC4.3, X1.18
SPI4_IRQ: IC4.168, X1.20
SPI4_MISO: IC4.4, X1.12
SPI4_MOSI: IC4.5, X1.14
SPI5_CLK: IC4.25, X1.23
SPI5_CSA: IC4.157, X1.29
SPI5_CSB: IC4.156, X1.31
SPI5_IRQ: IC4.79, JP8.2, X1.33
SPI5_MISO: IC4.26, X1.25
SPI5_MOSI: IC4.27, X1.27
VDD: C13.1, C14.1, C15.1, C16.1, C17.1, C18.1, C19.+, C20.1, C21.1, C22.1, C23.1, C24.1, C25.1, C26.1, C27.1, C28.1, C29.1, C30.1, IC4.15, IC4.23, IC4.36, IC4.49, IC4.62, IC4.72, IC4.82, IC4.96, IC4.99, IC4.118, IC4.131, IC4.136, IC4.149, IC4.159, IC4.171, IC4.172, JP1.NO, JP2.NO, L1.P$1, R11.1, R17.2
~FAULT: IC3.1, IC4.58, R13.2, X1.26, X2.15
~RESET: IC3.4, IC4.31, IC7.4, IC17.29, JP4.NC, R11.2, X1.24, X4.15

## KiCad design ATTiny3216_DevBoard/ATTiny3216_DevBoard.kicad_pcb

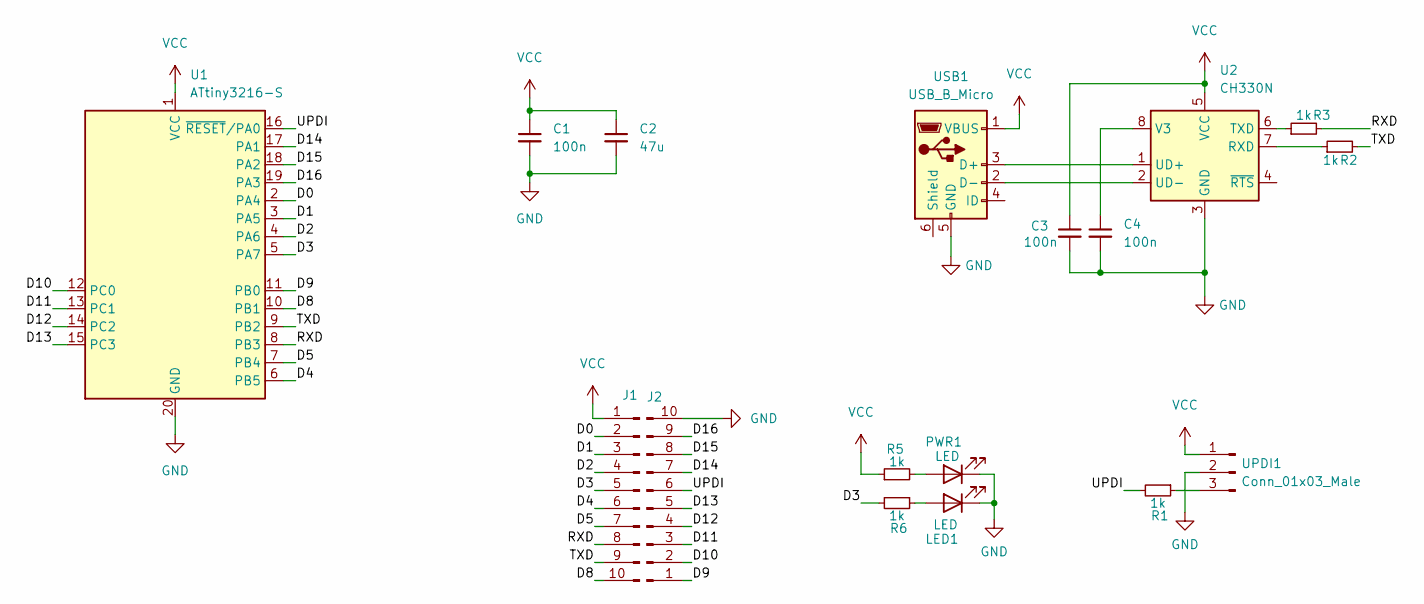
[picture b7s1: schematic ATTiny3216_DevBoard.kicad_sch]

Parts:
C1, C3, C4: 100n; C_0603_1608Metric_Pad1.08x0.95mm_HandSolder
C2: 47u; C_1206_3216Metric_Pad1.33x1.80mm_HandSolder
J1, J2: Conn_01x10_Male; PinHeader_1x10_P2.54mm_Vertical
LED1: LED; LED_0603_1608Metric_Pad1.05x0.95mm_HandSolder
PWR1: LED; LED_0603_1608Metric_Pad1.05x0.95mm_HandSolder
R1, R2, R3, R5, R6: 1k; R_0603_1608Metric_Pad0.98x0.95mm_HandSolder
U1: ATtiny3216-S; SOIC-20W_7.5x12.8mm_P1.27mm
U2: CH330N; SOIC-8_3.9x4.9mm_P1.27mm
UPDI1: Conn_01x03_Male; PinHeader_1x03_P2.54mm_Vertical
USB1: USB_B_Micro; USB_Micro-B_Amphenol_10104110_Horizontal

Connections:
/D0: J1.2, U1.2 (PA4)
/D1: J1.3, U1.3 (PA5)
/D2: J1.4, U1.4 (PA6)
/D3: J1.5, R6.2, U1.5 (PA7)
/D4: J1.6, U1.6 (PB5)
/D5: J1.7, U1.7 (PB4)
/D8: J1.10, U1.10 (PB1)
/D9: J2.1, U1.11 (PB0)
/D10: J2.2, U1.12 (PC0)
/D11: J2.3, U1.13 (PC1)
/D12: J2.4, U1.14 (PC2)
/D13: J2.5, U1.15 (PC3)
/D14: J2.7, U1.17 (PA1)
/D15: J2.8, U1.18 (PA2)
/D16: J2.9, U1.19 (PA3)
/RXD: J1.8, R3.2, U1.8 (PB3)
/TXD: J1.9, R2.2, U1.9 (PB2)
/UPDI: J2.6, R1.2, U1.16 (~RESET/PA0)
GND: C1.2, C2.2, C3.2, C4.2, J2.10, LED1.1 (K), PWR1.1 (K), U1.20 (GND), U2.3 (GND), UPDI1.2, USB1.5 (GND)
unnamed: LED1.2 (A), R6.1
unnamed: PWR1.2 (A), R5.2
unnamed: R3.1, U2.6 (TXD)
unnamed: R2.1, U2.7 (RXD)
unnamed: C4.1, U2.8 (V3)
unnamed: R1.1, UPDI1.3
unnamed: U2.2 (UD-), USB1.2 (D-)
unnamed: U2.1 (UD+), USB1.3 (D+)
VCC: C1.1, C2.1, C3.1, J1.1, R5.1, U1.1 (VCC), U2.5 (VCC), UPDI1.1, USB1.1 (VBUS)

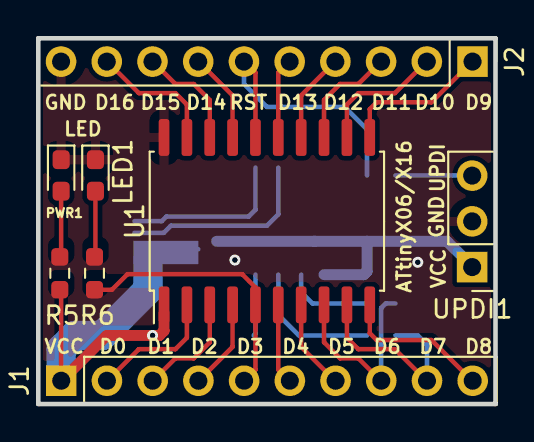
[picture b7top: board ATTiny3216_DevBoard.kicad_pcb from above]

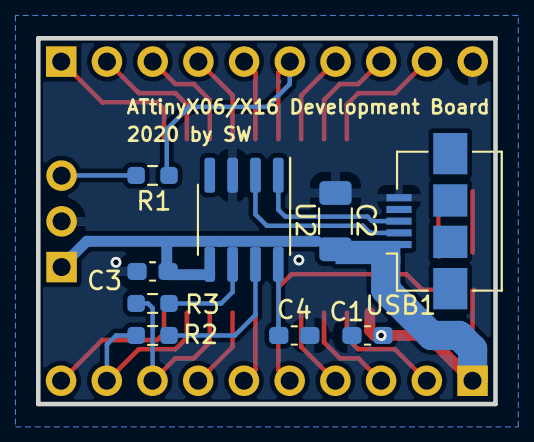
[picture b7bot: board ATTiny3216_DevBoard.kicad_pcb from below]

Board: 2 copper layers, 25.4 x 20.3 mm, 17 parts (9 on the bottom side), 28 nets.

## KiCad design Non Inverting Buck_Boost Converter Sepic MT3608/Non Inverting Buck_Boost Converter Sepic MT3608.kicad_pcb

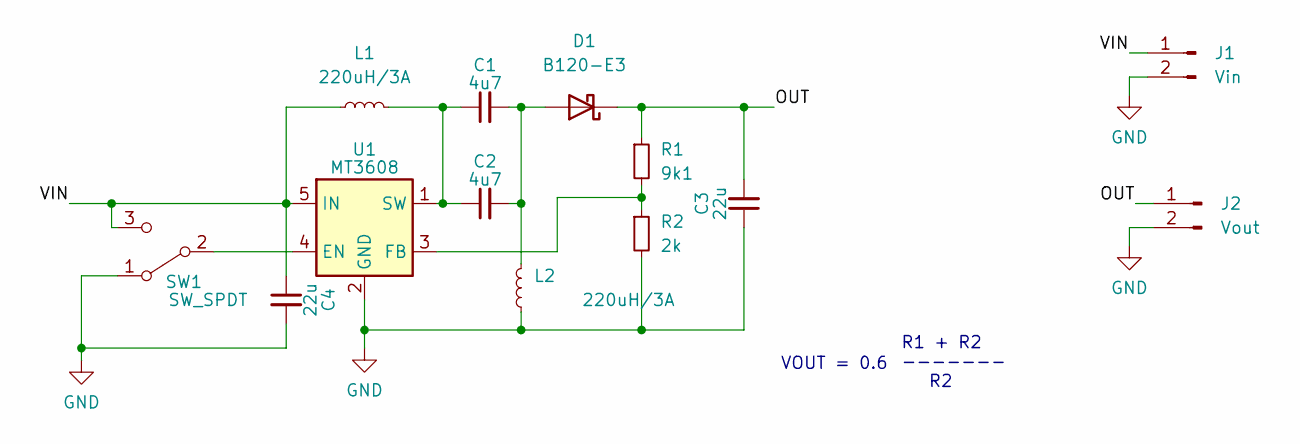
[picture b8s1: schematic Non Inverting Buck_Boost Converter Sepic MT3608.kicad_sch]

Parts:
C1, C2: 4u7; C_0805_2012Metric_Pad1.18x1.45mm_HandSolder
C3, C4: 22u; C_1206_3216Metric_Pad1.33x1.80mm_HandSolder
D1: B120-E3; D_SMA
J1: Vin; PinSocket_1x02_P2.54mm_Vertical
J2: Vout; PinSocket_1x02_P2.54mm_Vertical
L1, L2: 220uH/3A; L_Bourns_SRP7028A_7.3x6.6mm
R1: 9k1; R_0805_2012Metric_Pad1.20x1.40mm_HandSolder
R2: 2k; R_0805_2012Metric_Pad1.20x1.40mm_HandSolder
SW1: SW_SPDT; PinSocket_1x03_P2.54mm_Vertical
U1: MT3608; SOT-23-6

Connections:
/OUT: C3.2, D1.1 (K), J2.1, R1.1
/VIN: C4.1, J1.1, L1.1, SW1.3 (C), U1.5 (IN)
GND: C3.1, C4.2, J1.2, J2.2, L2.1, R2.2, SW1.1 (A), U1.2 (GND)
unnamed: C1.1, C2.1, L1.2, U1.1 (SW)
unnamed: C1.2, C2.2, D1.2 (A), L2.2
unnamed: R1.2, R2.1, U1.3 (FB)
unnamed: SW1.2 (B), U1.4 (EN)

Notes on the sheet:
R1 + R2 ------- R2
VOUT = 0.6

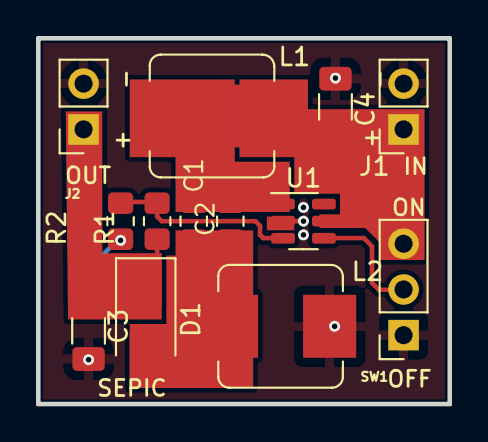
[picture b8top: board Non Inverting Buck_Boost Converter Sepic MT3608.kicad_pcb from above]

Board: 2 copper layers, 22.9 x 20.3 mm, 13 parts (0 on the bottom side), 7 nets.

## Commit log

2022-12-04 Add Single Switch PDM Control
2022-12-04 Add At Tiny Raw Board
2022-12-04 Add External Latch Power Board
2022-12-04 add esp32 board
2022-12-11 Add Non Inverting BuckBoost
2022-12-11 Add ATTiny3216_DevBoard
2022-12-11 add power supply
2022-12-14 Create fp-info-cache
2022-12-16 add latch power button board
2022-12-16 update latch
2022-12-17 add 78xx replacement
2022-12-17 add fpga referensi
2022-12-19 Add Power Bank
2022-12-30 add dcdc boost Converter

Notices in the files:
Non Inverting Buck_Boost Converter Sepic MT3608/Non Inverting Buck_Boost Converter Sepic MT3608.kicad_pcb:
CC-BY-SA
